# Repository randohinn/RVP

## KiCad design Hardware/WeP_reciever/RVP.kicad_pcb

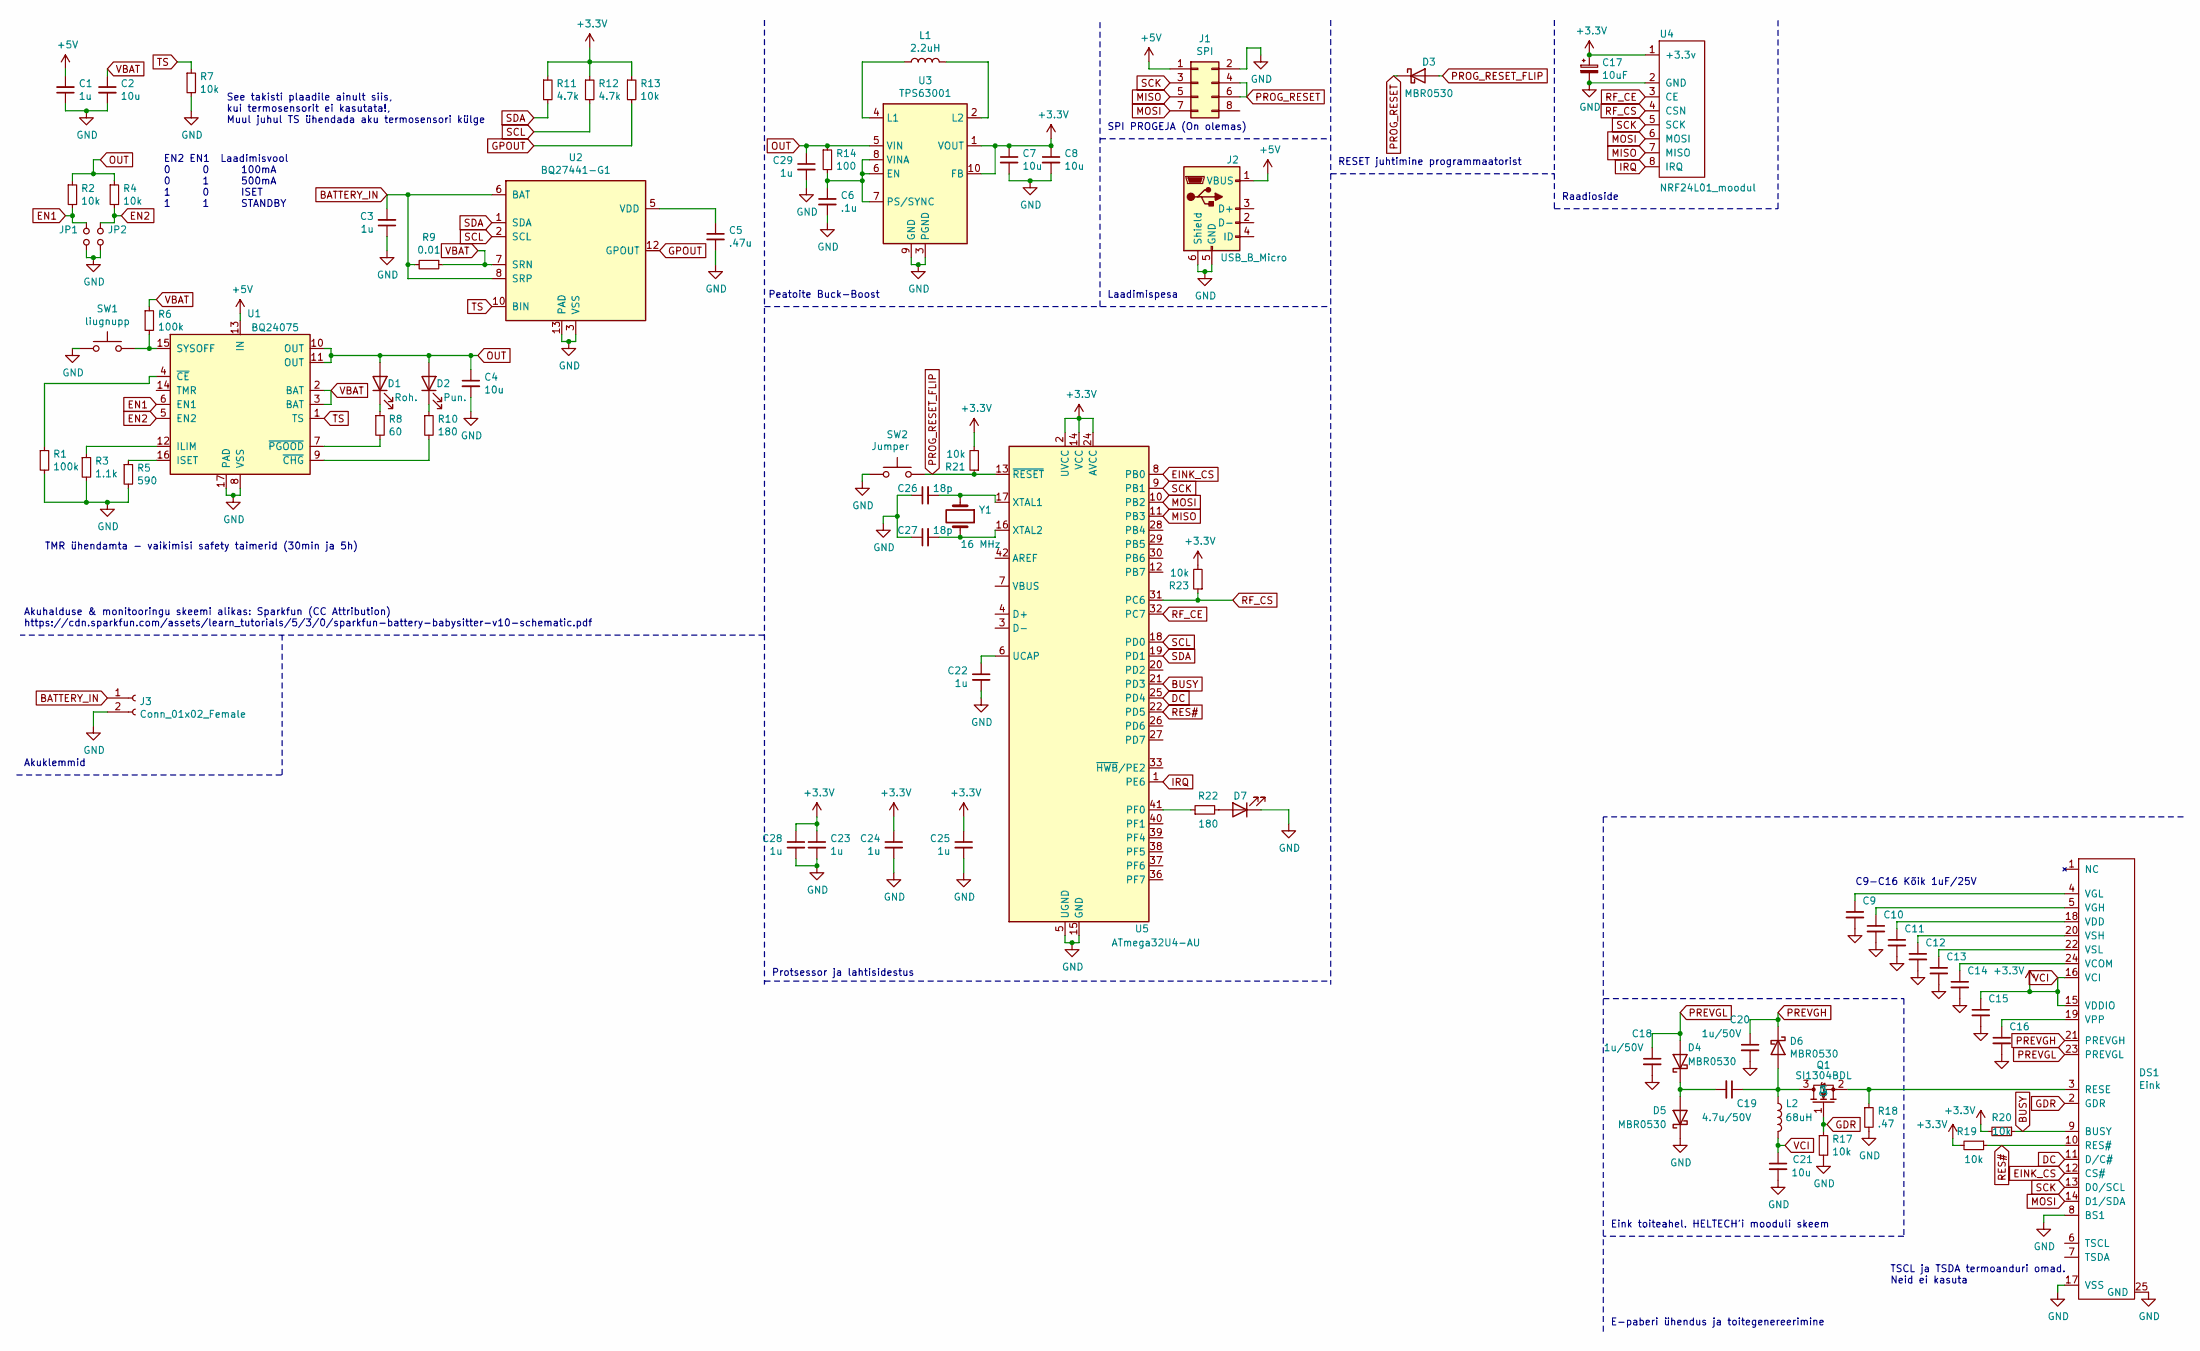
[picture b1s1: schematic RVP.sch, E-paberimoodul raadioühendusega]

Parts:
C1, C3, C9, C10, C11, C12, C13, C14, C15, C16, C22, C23, C24, C25, C28, C29: 1u; C_0603_1608Metric
C2, C4, C7, C8, C21: 10u; C_0603_1608Metric
C5: .47u; C_0603_1608Metric
C6: .1u; C_0603_1608Metric
C17: 10uF; CP_EIA-3528-15_AVX-H
C18, C20: 1u/50V; C_0603_1608Metric
C19: 4.7u/50V; C_0603_1608Metric
C26, C27: 18p; C_0603_1608Metric
D1: Roh.; LED_0603_1608Metric
D2: Pun.; LED_0603_1608Metric
D3, D4, D5, D6: MBR0530; D_SOD-123
D7: Sinine; LED_0603_1608Metric
DS1: Eink
J1: SPI; PinHeader_2x04_P2.54mm_Vertical
J2: USB_B_Micro; USB_Micro-B_Amphenol_10104110_Horizontal
J3: Conn_01x02_Female; Solderpads
JP1, JP2: Jumper_NO_Small; SolderJumper-2_P1.3mm_Open_Pad1.0x1.5mm
L1: 2.2uH; L_0603_1608Metric
L2: 68uH; L_0603_1608Metric
Q1: SI1304BDL; SOT-323_SC-70_Handsoldering
R1, R6: 100k; R_0603_1608Metric
R2, R4, R7, R13, R17, R19, R20, R21, R23: 10k; R_0603_1608Metric
R3: 1.1k; R_0603_1608Metric
R5: 590; R_0603_1608Metric
R8: 60; R_0603_1608Metric
R9: 0.01; R_0603_1608Metric
R10, R22: 180; R_0603_1608Metric
R11, R12: 4.7k; R_0603_1608Metric
R14: 100; R_0603_1608Metric
R18: .47; R_0603_1608Metric
SW1: liugnupp; MK12C02
SW2: Jumper; C_0603_1608Metric
U1: BQ24075; VQFN-16-1EP_3x3mm_P0.5mm_EP1.68x1.68mm
U2: BQ27441-G1; Texas_S-PDSO-N12
U3: TPS63001; Texas_DRC0010J_ThermalVias
U4: NRF24L01_moodul; NRF24L01 moodul SMD
U5: ATmega32U4-AU; TQFP-44_10x10mm_P0.8mm
Y1: 16 MHz; Crystal_SMD_TXC_7A-2Pin_5x3.2mm

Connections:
+5V: C1.2, J1.1, J2.1 (VBUS), U1.13 (IN)
BATTERY_IN: C3.2, J3.1, R9.2, U2.6 (BAT), U2.8 (SRP)
BUSY: DS1.9 (BUSY), R20.1, U5.21 (PD3)
DC: DS1.11 (D/C#), U5.25 (PD4)
EINK_CS: DS1.12 (CS#), U5.8 (PB0)
EN1: JP1.1, R2.2, U1.6 (EN1)
EN2: JP2.1, R4.2, U1.5 (EN2)
GDR: DS1.2 (GDR), Q1.1 (G), R17.1
GND: C1.1, C2.2, C3.1, C4.2, C5.2, C6.2, C7.2, C8.2, C9.2, C10.2, C11.2, C12.2, C13.2, C14.2, C15.2, C16.2, C17.2, C18.2, C20.2, C21.2, C22.2, C23.2, C24.2, C25.2, C26.1, C27.1, C28.2, C29.2, D5.1 (K), D7.1 (K), DS1.8 (BS1), DS1.17 (VSS), DS1.25 (GND), J1.2, J2.5 (GND), J2.6 (Shield), J3.2, JP1.2, JP2.2, R1.2, R3.2, R5.2, R7.2, R17.2, R18.2, SW1.2, SW2.1, U1.8 (VSS), U1.17 (PAD), U2.3 (VSS), U2.13 (PAD), U3.3 (PGND), U3.9 (GND), U3.11 (PGND), U4.2 (GND), U5.5 (UGND), U5.15 (GND), U5.23 (GND), U5.35 (GND), U5.43 (GND)
GPOUT: R13.2, U2.12 (GPOUT)
IRQ: U4.8 (IRQ), U5.1 (PE6)
MISO: J1.5, U4.7 (MISO), U5.11 (PB3)
MOSI: DS1.14 (D1/SDA), J1.7, U4.6 (MOSI), U5.10 (PB2)
unnamed: C5.1, U2.5 (VDD)
unnamed: C6.1, R14.2, U3.6 (EN), U3.7 (PS/SYNC), U3.8 (VINA)
unnamed: C9.1, DS1.4 (VGL)
unnamed: C10.1, DS1.5 (VGH)
unnamed: C11.1, DS1.18 (VDD)
unnamed: C12.1, DS1.20 (VSH)
unnamed: C13.1, DS1.22 (VSL)
unnamed: C14.1, DS1.24 (VCOM)
unnamed: C16.1, DS1.19 (VPP)
unnamed: C19.1, D6.2 (A), L2.1, Q1.3 (D)
unnamed: C19.2, D4.1 (K), D5.2 (A)
unnamed: C22.1, U5.6 (UCAP)
unnamed: C26.2, U5.17 (XTAL1), Y1.1
unnamed: C27.2, U5.16 (XTAL2), Y1.2
unnamed: D1.1 (K), R8.1
unnamed: D2.1 (K), R10.1
unnamed: D7.2 (A), R22.2
unnamed: DS1.3 (RESE), Q1.2 (S), R18.1
unnamed: L1.1, U3.4 (L1)
unnamed: L1.2, U3.2 (L2)
unnamed: R1.1, U1.4 (~CE)
unnamed: R3.1, U1.12 (ILIM)
unnamed: R5.1, U1.16 (ISET)
unnamed: R6.2, SW1.1, U1.15 (SYSOFF)
unnamed: R8.2, U1.7 (~PGOOD)
unnamed: R10.2, U1.9 (~CHG)
unnamed: R22.1, U5.41 (PF0)
OUT: C4.1, C29.1, D1.2 (A), D2.2 (A), R2.1, R4.1, R14.1, U1.10 (OUT), U1.11 (OUT), U3.5 (VIN)
PREVGH: C20.1, D6.1 (K), DS1.21 (PREVGH)
PREVGL: C18.1, D4.2 (A), DS1.23 (PREVGL)
PROG_RESET: D3.1 (K), J1.4, J1.6
PROG_RESET_FLIP: D3.2 (A), R21.1, SW2.2, U5.13 (~RESET)
RES#: DS1.10 (RES#), R19.1, U5.22 (PD5)
RF_CE: U4.3 (CE), U5.32 (PC7)
RF_CS: R23.1, U4.4 (CSN), U5.31 (PC6)
SCK: DS1.13 (D0/SCL), J1.3, U4.5 (SCK), U5.9 (PB1)
SCL: R12.2, U2.2 (SCL), U5.18 (PD0)
SDA: R11.2, U2.1 (SDA), U5.19 (PD1)
TS: R7.1, U1.1 (TS), U2.10 (BIN)
VBAT: C2.1, R6.1, R9.1, U1.2 (BAT), U1.3 (BAT), U2.7 (SRN)
VCI: C7.1, C8.1, C15.1, C17.1, C21.1, C23.1, C24.1, C25.1, C28.1, DS1.15 (VDDIO), DS1.16 (VCI), L2.2, R11.1, R12.1, R13.1, R19.2, R20.2, R21.2, R23.2, U3.1 (VOUT), U3.10 (FB), U4.1 (+3.3v), U5.2 (UVCC), U5.14 (VCC), U5.24 (AVCC), U5.34 (VCC), U5.44 (AVCC)

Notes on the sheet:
Akuhalduse & monitooringu skeemi alikas: Sparkfun (CC Attribution) https://cdn.sparkfun.com/assets/learn_tutorials/5/3/0/sparkfun-battery-babysitter-v10-schematic.pdf
See takisti plaadile ainult siis, kui termosensorit ei kasutata!, Muul juhul TS ühendada aku termosensori külge
TMR ühendamta - vaikimisi safety taimerid (30min ja 5h)
EN2 EN1 Laadimisvool 0 0 100mA 0 1 500mA 1 0 ISET 1 1 STANDBY
Peatoite Buck-Boost
SPI PROGEJA (On olemas)
Laadimispesa
RESET juhtimine programmaatorist
Raadioside
TSCL ja TSDA termoanduri omad. Neid ei kasuta
Eink toiteahel. HELTECH'i mooduli skeem
C9-C16 Kõik 1uF/25V
E-paberi ühendus ja toitegenereerimine
Protsessor ja lahtisidestus
Akuklemmid

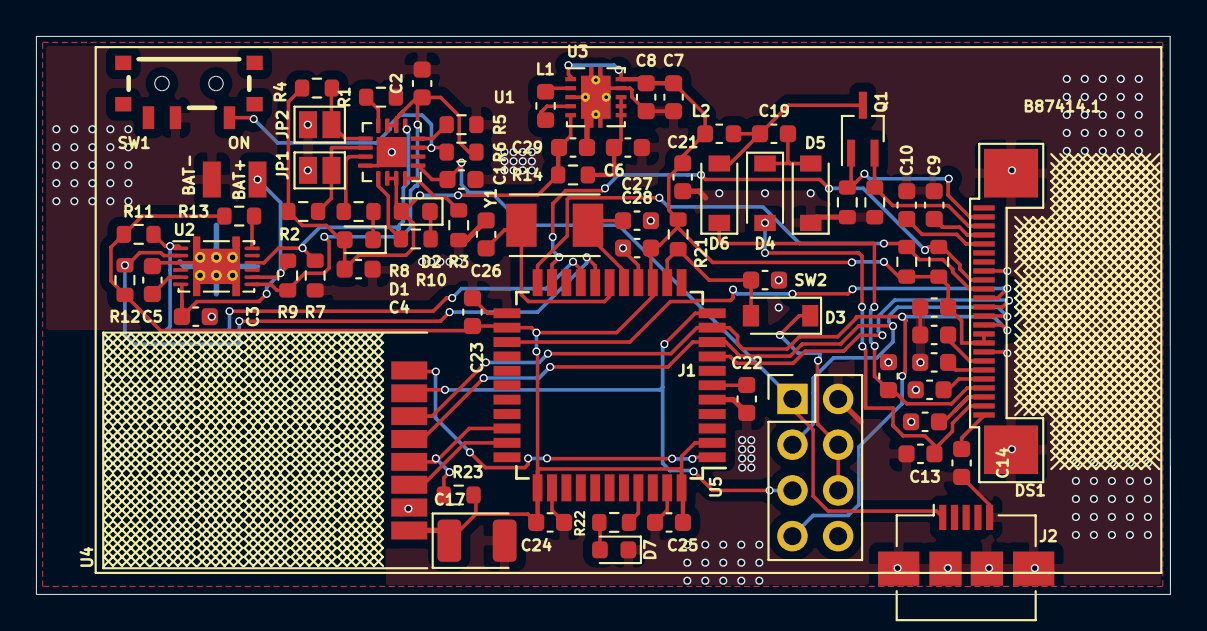
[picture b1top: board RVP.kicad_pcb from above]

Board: 2 copper layers, 63.0 x 31.0 mm, 74 parts (0 on the bottom side), 54 nets.

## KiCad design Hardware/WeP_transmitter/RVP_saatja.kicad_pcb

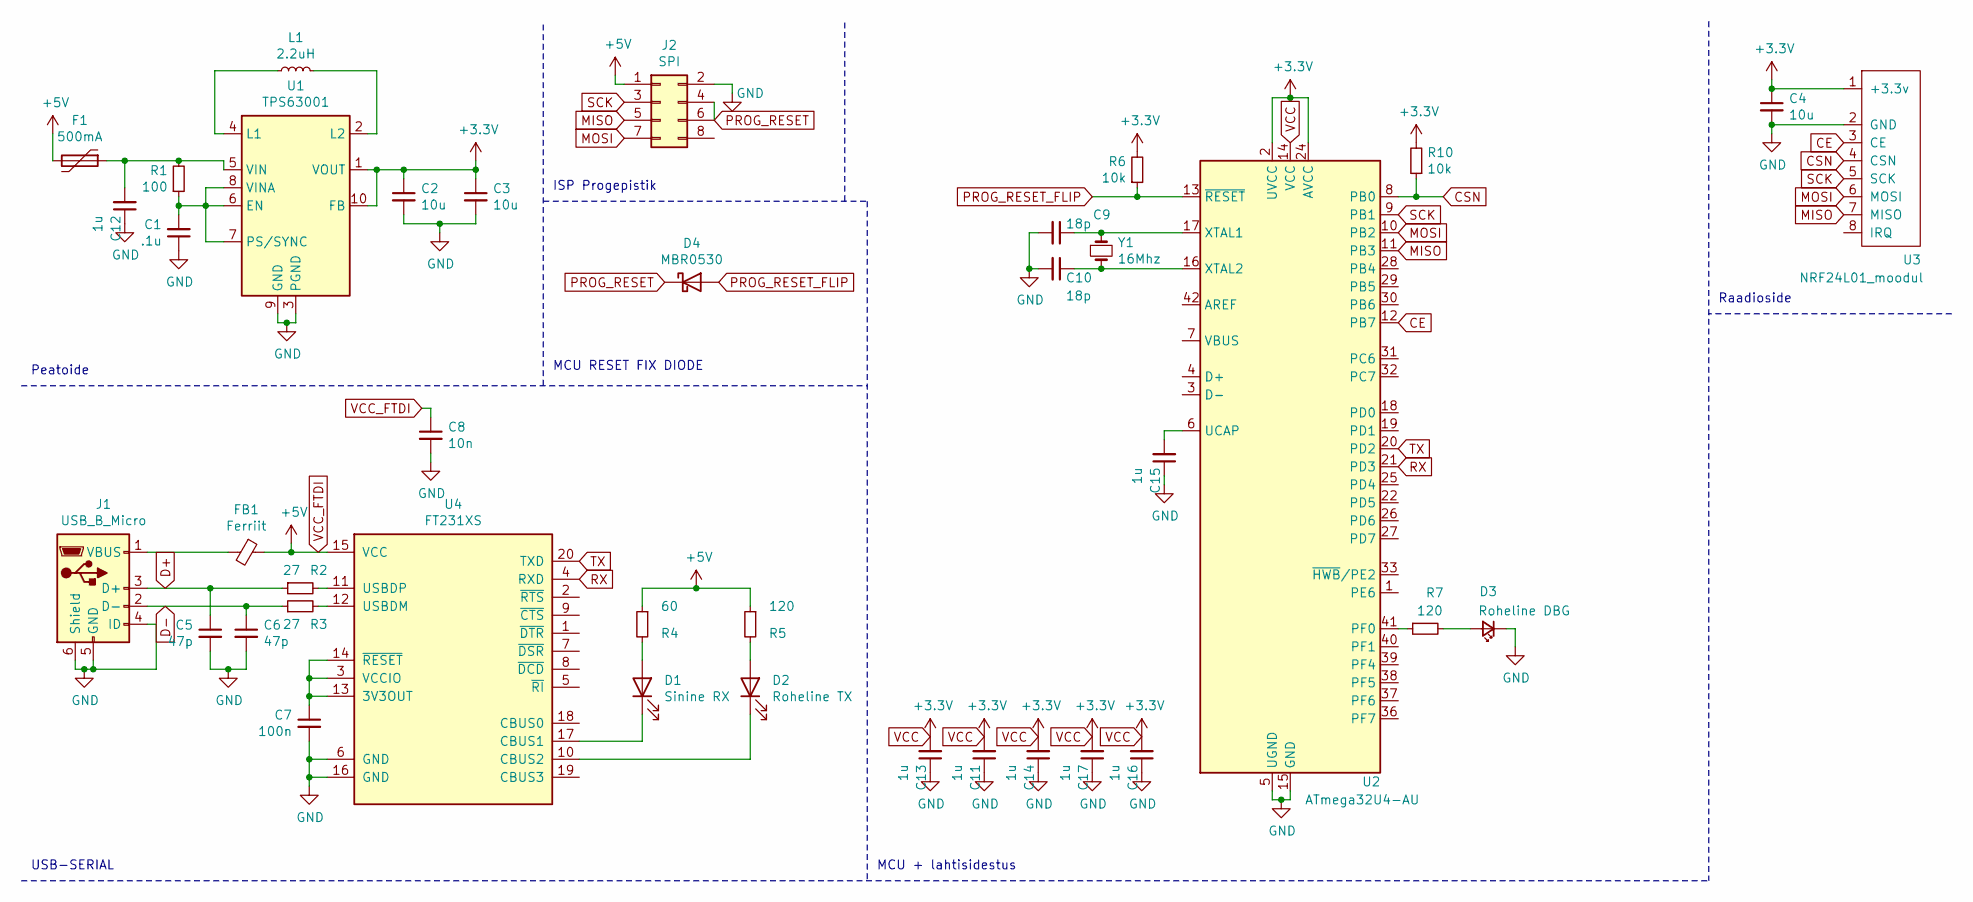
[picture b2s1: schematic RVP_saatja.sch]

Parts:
C1: .1u; C_0603_1608Metric
C2, C3: 10u; C_0603_1608Metric
C4: 10u; CP_EIA-3528-15_AVX-H
C5, C6: 47p; C_0603_1608Metric
C7: 100n; C_0603_1608Metric
C8: 10n; C_0603_1608Metric
C9, C10: 18p; C_0603_1608Metric
C11, C12, C13, C14, C15, C16, C17: 1u; C_0603_1608Metric
D1: Sinine RX; LED_0603_1608Metric
D2: Roheline TX; LED_0603_1608Metric
D3: Roheline DBG; LED_0603_1608Metric
D4: MBR0530; D_SOD-123
F1: 500mA; Fuse_1206_3216Metric
FB1: Ferriit; L_0603_1608Metric
J1: USB_B_Micro; USB_Micro-B_Amphenol_10104110_Horizontal
J2: SPI; PinHeader_2x04_P2.54mm_Vertical
L1: 2.2uH; L_0603_1608Metric
R1: 100; R_0603_1608Metric
R2, R3: 27; R_0603_1608Metric
R4: 60; R_0603_1608Metric
R5, R7: 120; R_0603_1608Metric
R6, R10: 10k; R_0603_1608Metric
U1: TPS63001; Texas_DRC0010J_ThermalVias
U2: ATmega32U4-AU; TQFP-44_10x10mm_P0.8mm
U3: NRF24L01_moodul; NRF24L01 moodul SMD
U4: FT231XS; SSOP-20_3.9x8.7mm_P0.635mm
Y1: 16Mhz; Crystal_SMD_TXC_7A-2Pin_5x3.2mm

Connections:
CE: U2.12 (PB7), U3.3 (CE)
CSN: R10.1, U2.8 (PB0), U3.4 (CSN)
D+: C5.1, J1.3 (D+), R2.1
D-: C6.1, J1.2 (D-), R3.1
GND: C1.1, C2.2, C3.2, C4.2, C5.2, C6.2, C7.2, C8.2, C9.2, C10.2, C11.1, C12.1, C13.1, C14.1, C15.1, C16.1, C17.1, D3.1 (K), J1.4 (ID), J1.5 (GND), J1.6 (Shield), J2.2, U1.3 (PGND), U1.9 (GND), U1.11 (PGND), U2.5 (UGND), U2.15 (GND), U2.23 (GND), U2.35 (GND), U2.43 (GND), U3.2 (GND), U4.6 (GND), U4.16 (GND)
MISO: J2.5, U2.11 (PB3), U3.7 (MISO)
MOSI: J2.7, U2.10 (PB2), U3.6 (MOSI)
unnamed: C1.2, R1.1, U1.6 (EN), U1.7 (PS/SYNC), U1.8 (VINA)
unnamed: C7.1, U4.3 (VCCIO), U4.13 (3V3OUT), U4.14 (~RESET)
unnamed: C9.1, U2.17 (XTAL1), Y1.1
unnamed: C10.1, U2.16 (XTAL2), Y1.2
unnamed: C12.2, F1.1, R1.2, U1.5 (VIN)
unnamed: C15.2, U2.6 (UCAP)
unnamed: D1.1 (K), U4.17 (CBUS1)
unnamed: D1.2 (A), R4.2
unnamed: D2.1 (K), U4.10 (CBUS2)
unnamed: D2.2 (A), R5.2
unnamed: D3.2 (A), R7.2
unnamed: FB1.2, J1.1 (VBUS)
unnamed: L1.1, U1.4 (L1)
unnamed: L1.2, U1.2 (L2)
unnamed: R2.2, U4.11 (USBDP)
unnamed: R3.2, U4.12 (USBDM)
unnamed: R7.1, U2.41 (PF0)
PROG_RESET: D4.1 (K), J2.4, J2.6
PROG_RESET_FLIP: D4.2 (A), R6.1, U2.13 (~RESET)
RX: U2.21 (PD3), U4.4 (RXD)
SCK: J2.3, U2.9 (PB1), U3.5 (SCK)
TX: U2.20 (PD2), U4.20 (TXD)
VCC: C2.1, C3.1, C4.1, C11.2, C13.2, C14.2, C16.2, C17.2, R6.2, R10.2, U1.1 (VOUT), U1.10 (FB), U2.2 (UVCC), U2.14 (VCC), U2.24 (AVCC), U2.34 (VCC), U2.44 (AVCC), U3.1 (+3.3v)
VCC_FTDI: C8.1, F1.2, FB1.1, J2.1, R4.1, R5.1, U4.15 (VCC)

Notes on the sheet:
Raadioside
Peatoide
USB-SERIAL
ISP Progepistik
MCU RESET FIX DIODE
MCU + lahtisidestus

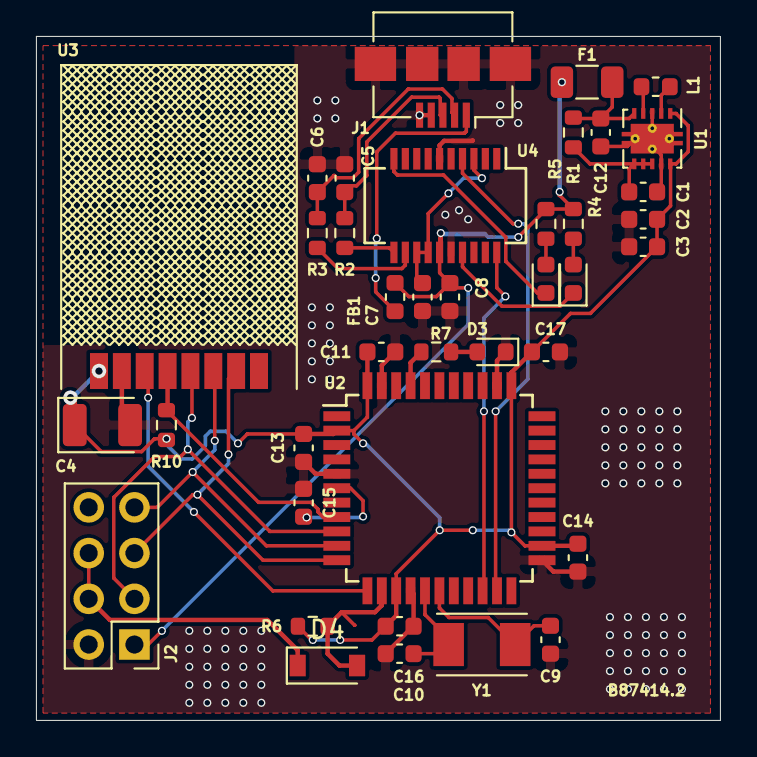
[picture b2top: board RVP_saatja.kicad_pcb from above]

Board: 2 copper layers, 38.0 x 38.0 mm, 39 parts (0 on the bottom side), 31 nets.

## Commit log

2021-02-11 Lisan windowsi rakenduse ja akukontrolliga vastuvõtja
2021-02-11 Delphi ide lolluste fix
